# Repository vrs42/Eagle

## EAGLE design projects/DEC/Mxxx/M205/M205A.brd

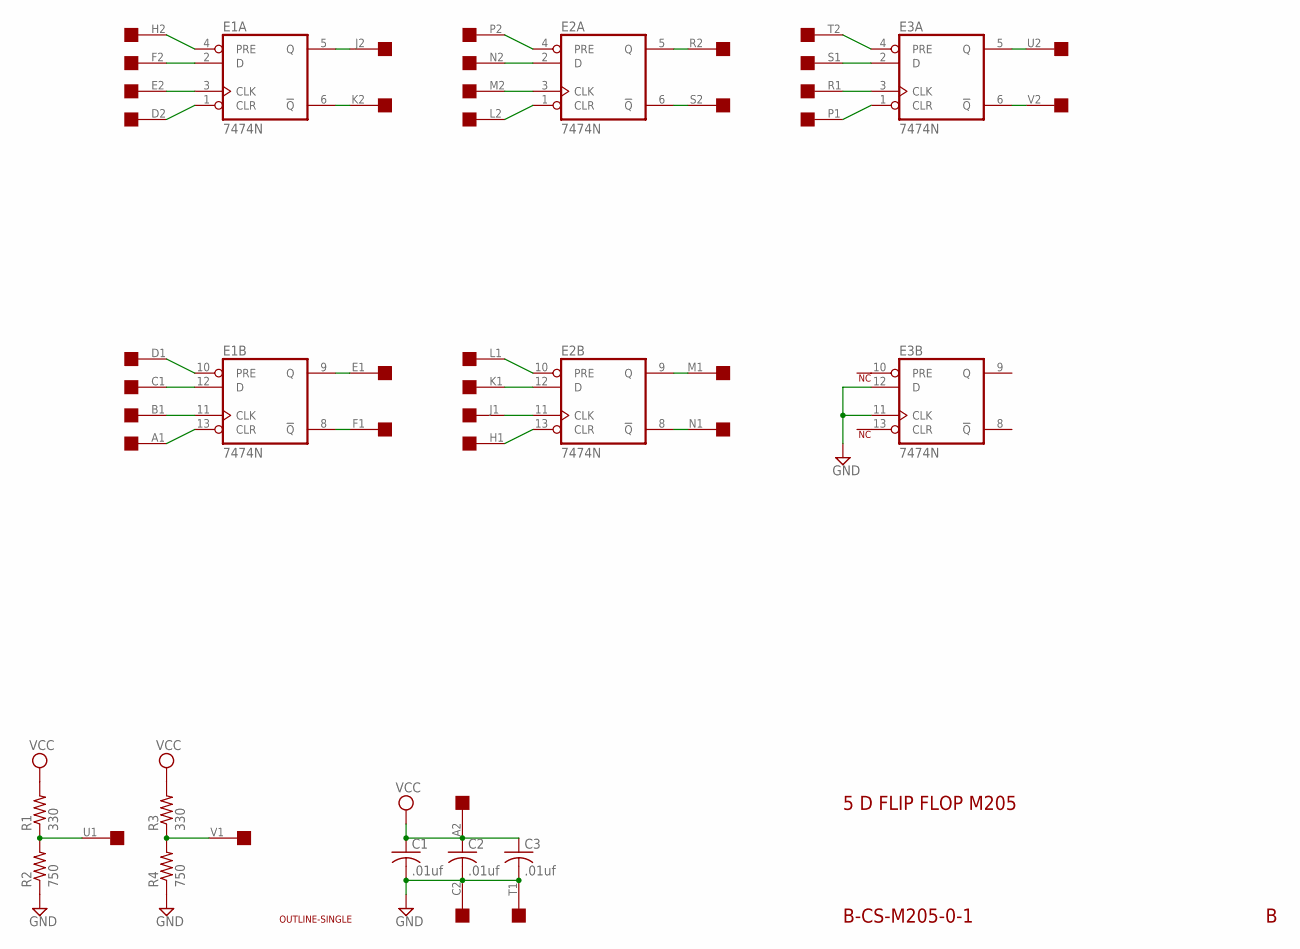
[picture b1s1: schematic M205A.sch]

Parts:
C1, C2, C3: .01uf; C050-025X075
E1, E2, E3: 7474N; DIL14
R1, R3: 330; 0207/10
R2, R4: 750; 0207/10
U$1: OUTLINE-SINGLE; SINGLE
U$2: EDGE-2CONNECTOR; EDGE-CON2

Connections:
GND: C1.2, C2.2, C3.2, E1.7 (GND), E2.7 (GND), E3.7 (GND), E3.11 (CLK), E3.12 (D), R2.1, R4.1, U$2.C2, U$2.T1
unnamed: R1.1, R2.2, U$2.U1
unnamed: R3.1, R4.2, U$2.V1
unnamed: E1.6 (!Q), U$2.K2
unnamed: E1.5 (Q), U$2.J2
unnamed: E1.2 (D), U$2.F2
unnamed: E1.4 (PRE), U$2.H2
unnamed: E1.3 (CLK), U$2.E2
unnamed: E1.1 (CLR), U$2.D2
unnamed: E2.1 (CLR), U$2.L2
unnamed: E2.3 (CLK), U$2.M2
unnamed: E2.2 (D), U$2.N2
unnamed: E2.4 (PRE), U$2.P2
unnamed: E2.6 (!Q), U$2.S2
unnamed: E2.5 (Q), U$2.R2
unnamed: E3.1 (CLR), U$2.P1
unnamed: E3.3 (CLK), U$2.R1
unnamed: E3.2 (D), U$2.S1
unnamed: E3.6 (!Q), U$2.V2
unnamed: E3.5 (Q), U$2.U2
unnamed: E3.4 (PRE), U$2.T2
unnamed: E1.13 (CLR), U$2.A1
unnamed: E1.11 (CLK), U$2.B1
unnamed: E1.10 (PRE), U$2.D1
unnamed: E1.8 (!Q), U$2.F1
unnamed: E1.9 (Q), U$2.E1
unnamed: E1.12 (D), U$2.C1
unnamed: E2.13 (CLR), U$2.H1
unnamed: E2.11 (CLK), U$2.J1
unnamed: E2.12 (D), U$2.K1
unnamed: E2.10 (PRE), U$2.L1
unnamed: E2.9 (Q), U$2.M1
unnamed: E2.8 (!Q), U$2.N1
VCC: C1.1, C2.1, C3.1, E1.14 (VCC), E2.14 (VCC), E3.14 (VCC), R1.2, R3.2, U$2.A2

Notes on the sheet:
B-CS-M205-0-1
5 D FLIP FLOP M205

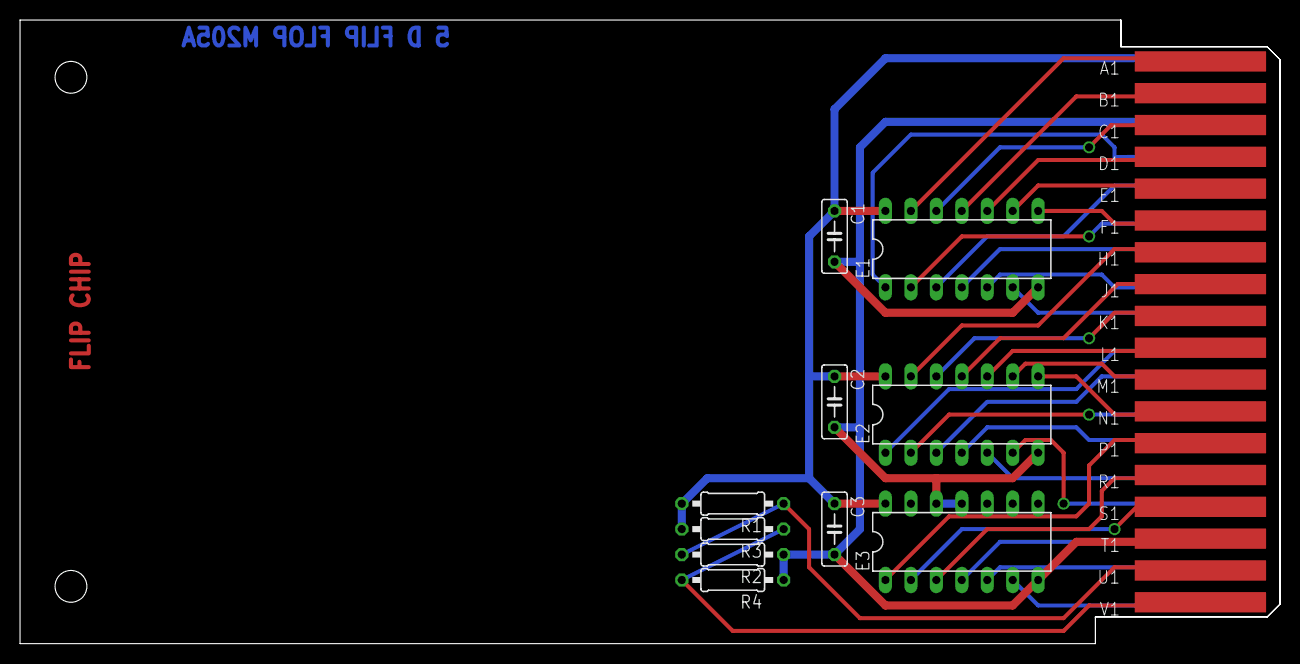
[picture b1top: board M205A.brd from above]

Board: 2 copper layers, 125.7 x 62.2 mm, 12 parts (0 on the bottom side), 34 nets.

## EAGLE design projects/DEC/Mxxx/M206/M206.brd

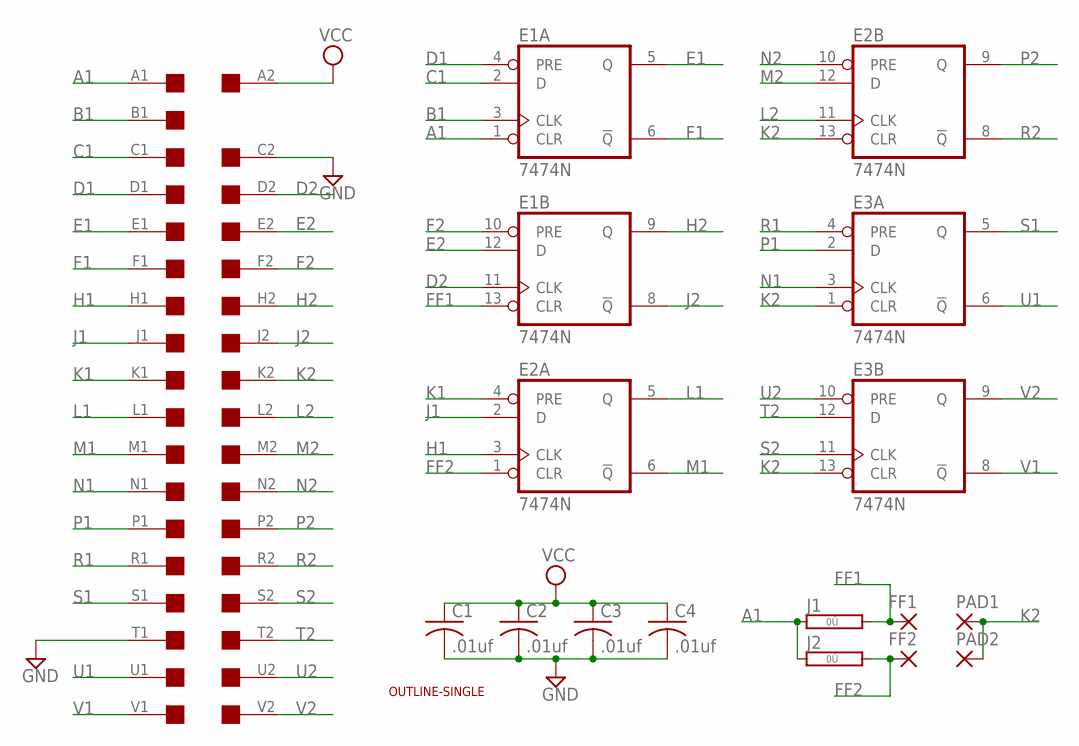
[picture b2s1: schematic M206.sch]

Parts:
C1, C2, C3, C4: .01uf; C050-025X075
E1, E2, E3: 7474N; DIL14
FF1, FF2: 1,6/0,8
J1, J2: 0R; 0R/10
PAD1, PAD2: 1,6/0,8
U$1: OUTLINE-SINGLE; SINGLE
U$4: SINGLE; EDGE-CON2

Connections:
A1: E1.1 (CLR), J1.1, J2.1, U$4.A1
B1: E1.3 (CLK), U$4.B1
C1: E1.2 (D), U$4.C1
D1: E1.4 (PRE), U$4.D1
D2: E1.11 (CLK), U$4.D2
E1: E1.5 (Q), U$4.E1
E2: E1.12 (D), U$4.E2
F1: E1.6 (!Q), U$4.F1
F2: E1.10 (PRE), U$4.F2
FF1: E1.13 (CLR), FF1.1, J1.2
FF2: E2.1 (CLR), FF2.1, J2.2
GND: C1.2, C2.2, C3.2, C4.2, E1.7 (GND), E2.7 (GND), E3.7 (GND), U$4.C2, U$4.T1
H1: E2.3 (CLK), U$4.H1
H2: E1.9 (Q), U$4.H2
J1: E2.2 (D), U$4.J1
J2: E1.8 (!Q), U$4.J2
K1: E2.4 (PRE), U$4.K1
K2: E2.13 (CLR), E3.1 (CLR), E3.13 (CLR), PAD1.1, PAD2.1, U$4.K2
L1: E2.5 (Q), U$4.L1
L2: E2.11 (CLK), U$4.L2
M1: E2.6 (!Q), U$4.M1
M2: E2.12 (D), U$4.M2
N1: E3.3 (CLK), U$4.N1
N2: E2.10 (PRE), U$4.N2
P1: E3.2 (D), U$4.P1
P2: E2.9 (Q), U$4.P2
R1: E3.4 (PRE), U$4.R1
R2: E2.8 (!Q), U$4.R2
S1: E3.5 (Q), U$4.S1
S2: E3.11 (CLK), U$4.S2
T2: E3.12 (D), U$4.T2
U1: E3.6 (!Q), U$4.U1
U2: E3.10 (PRE), U$4.U2
V1: E3.8 (!Q), U$4.V1
V2: E3.9 (Q), U$4.V2
VCC: C1.1, C2.1, C3.1, C4.1, E1.14 (VCC), E2.14 (VCC), E3.14 (VCC), U$4.A2

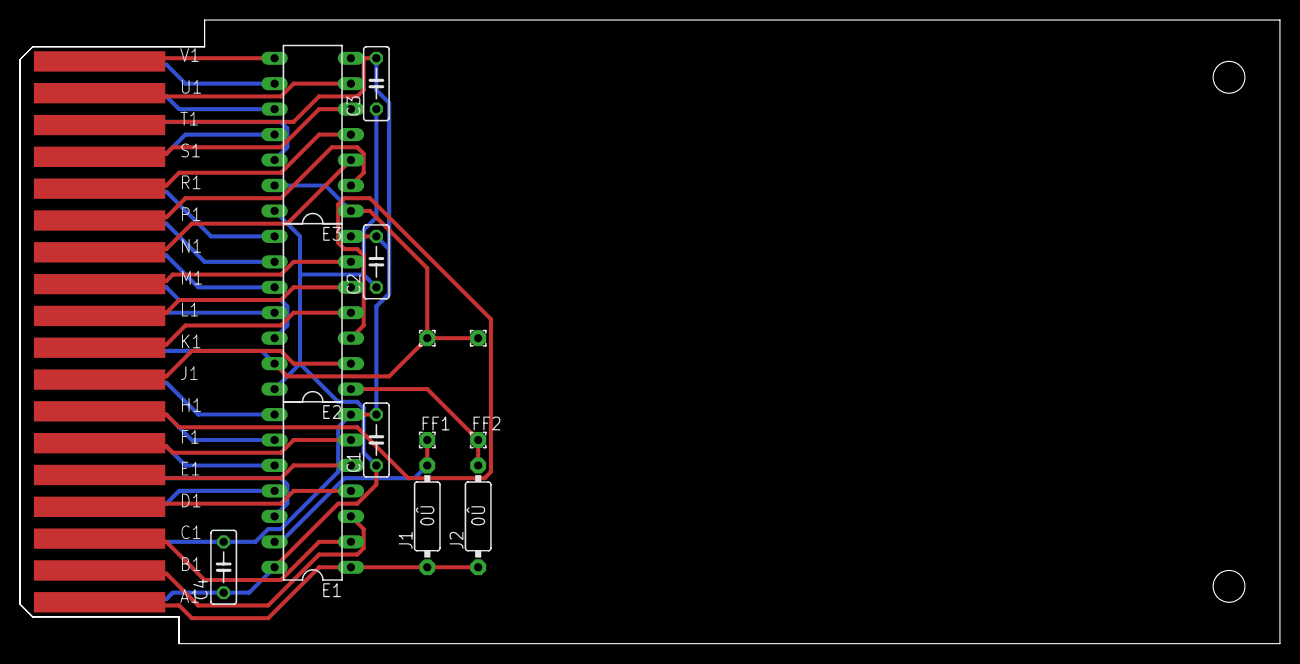
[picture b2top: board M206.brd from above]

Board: 2 copper layers, 125.7 x 62.2 mm, 15 parts (0 on the bottom side), 36 nets.

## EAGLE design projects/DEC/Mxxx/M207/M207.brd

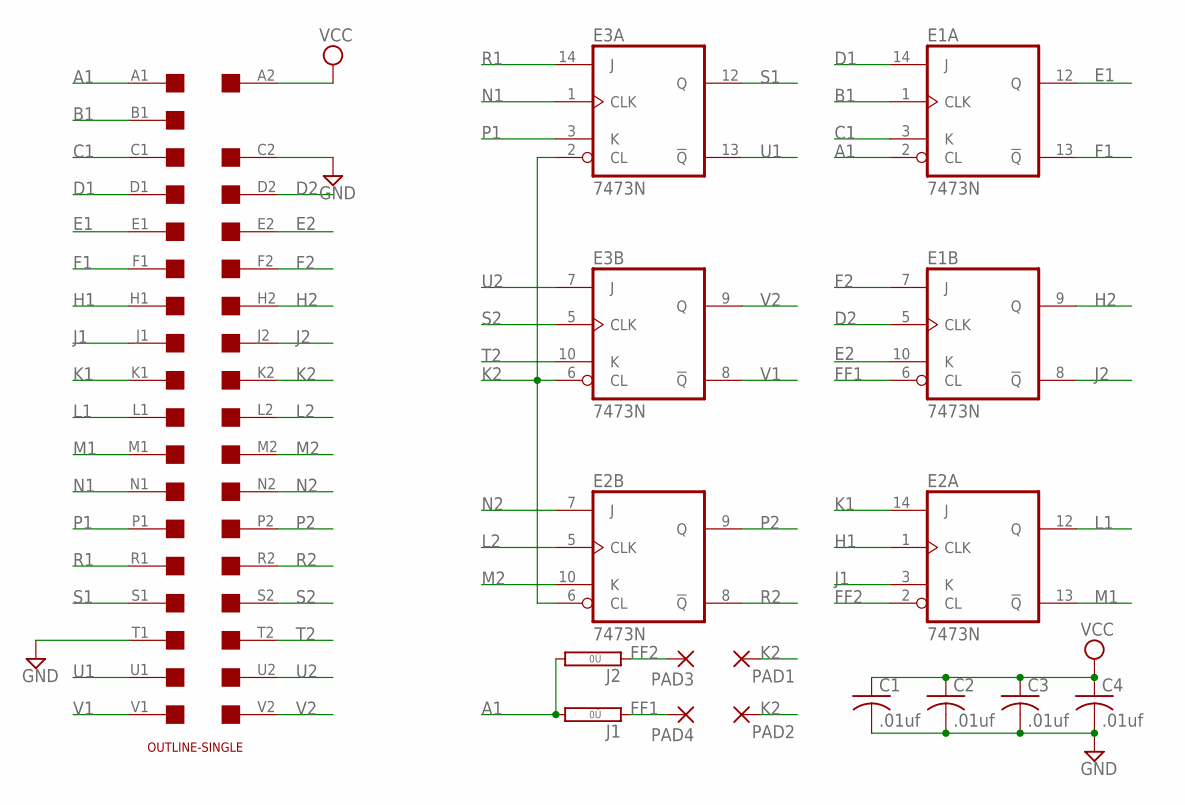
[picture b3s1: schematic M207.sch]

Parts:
C1, C2, C3, C4: .01uf; C050-025X075
E1, E2, E3: 7473N; DIL14
J1, J2: 0R; 0R/10
PAD1, PAD2, PAD3, PAD4: 1,6/0,8
U$1: SINGLE; EDGE-CON2
U$4: OUTLINE-SINGLE; SINGLE

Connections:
A1: E1.2 (CL), J1.2, J2.2, U$1.A1
B1: E1.1 (CLK), U$1.B1
C1: E1.3 (K), U$1.C1
D1: E1.14 (J), U$1.D1
D2: E1.5 (CLK), U$1.D2
E1: E1.12 (Q), U$1.E1
E2: E1.10 (K), U$1.E2
F1: E1.13 (!Q), U$1.F1
F2: E1.7 (J), U$1.F2
FF1: E1.6 (CL), J1.1, PAD4.1
FF2: E2.2 (CL), J2.1, PAD3.1
GND: C1.2, C2.2, C3.2, C4.2, E1.11 (GND), E2.11 (GND), E3.11 (GND), U$1.C2, U$1.T1
H1: E2.1 (CLK), U$1.H1
H2: E1.9 (Q), U$1.H2
J1: E2.3 (K), U$1.J1
J2: E1.8 (!Q), U$1.J2
K1: E2.14 (J), U$1.K1
K2: E2.6 (CL), E3.2 (CL), E3.6 (CL), PAD1.1, PAD2.1, U$1.K2
L1: E2.12 (Q), U$1.L1
L2: E2.5 (CLK), U$1.L2
M1: E2.13 (!Q), U$1.M1
M2: E2.10 (K), U$1.M2
N1: E3.1 (CLK), U$1.N1
N2: E2.7 (J), U$1.N2
P1: E3.3 (K), U$1.P1
P2: E2.9 (Q), U$1.P2
R1: E3.14 (J), U$1.R1
R2: E2.8 (!Q), U$1.R2
S1: E3.12 (Q), U$1.S1
S2: E3.5 (CLK), U$1.S2
T2: E3.10 (K), U$1.T2
U1: E3.13 (!Q), U$1.U1
U2: E3.7 (J), U$1.U2
V1: E3.8 (!Q), U$1.V1
V2: E3.9 (Q), U$1.V2
VCC: C1.1, C2.1, C3.1, C4.1, E1.4 (VCC), E2.4 (VCC), E3.4 (VCC), U$1.A2

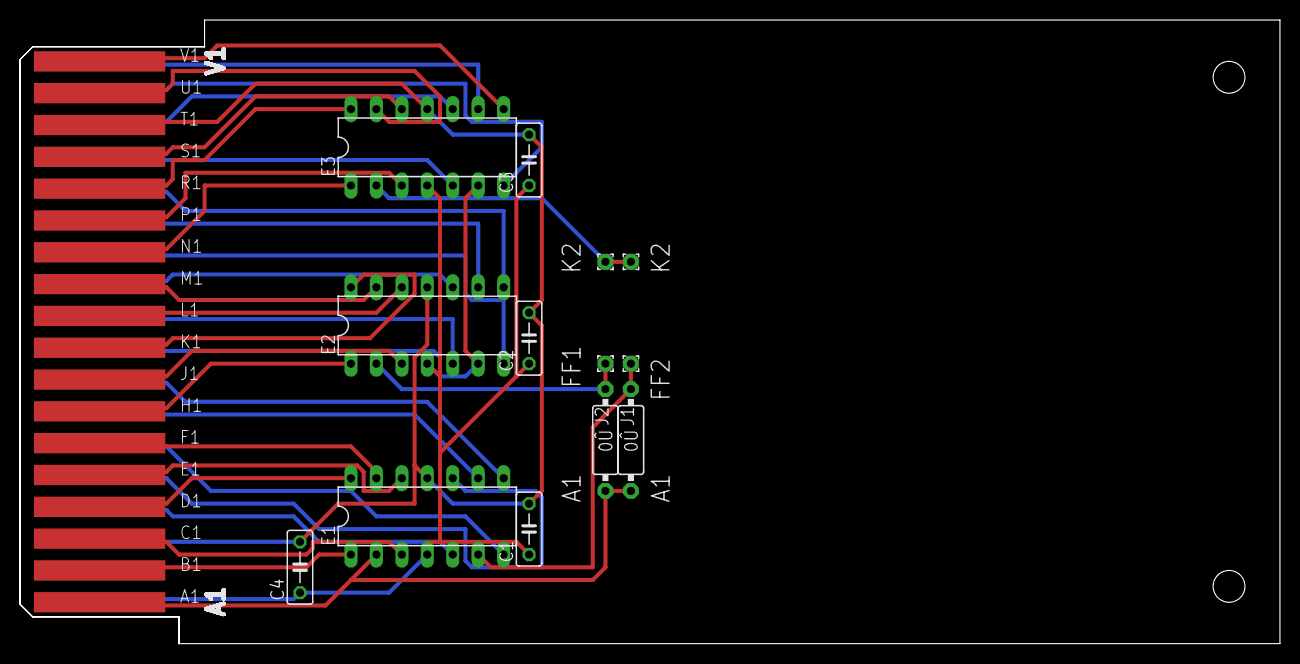
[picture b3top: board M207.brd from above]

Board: 2 copper layers, 125.7 x 62.2 mm, 15 parts (0 on the bottom side), 36 nets.
